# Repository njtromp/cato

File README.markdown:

# What's it all about
This project started slightly after I bought a sail boat, an Amigo 27 to be precisely.
At the time I bought the boat I did notice that the log (speed indicator) was not working
but that didn't bother me much. There where much, more important things, that needed my
attention. It is a mechanical VDO SumLog. There where two reasons for the log not to function.

1. a broken inner cable
2. a rusted impeller that does not turn

These two causes combined with the fact that replacement parts are hard to get your hands on
and the fact that I had a spare GPS Bluetooth dongle started me thinking. What if I can use
the GPS dongle for determining the speed and have a small (like a Raspberry PI) computer
control a electronic motor that drives the speed gauge?

## From RPM to knots and visa versa
I run some experiments using a cordless screwdriver for determining the RPM/knots settings.
It turned out to be about 100 RPM per knot :-). 

# Components
I needed some different components to get everything working

## Hardware
* a small computer
* a Bluetooth GPS dongle
* a USB Bluetooth dongle, for connecting the GPS to the computer
* a motor control unit that is capable of driving the electronic motor
* a electronic motor that is capable of runnning at 800-900 RPM with enough torque that will
be attached to the remainder of the inner cable
* a speed sensor for determining the RPM of the electronic motor (needed for feedback loop)

After some Googling and browsing the internet I come to the following shoppinglist:

* a Raspberry PI B+ (small, low power consumption, 4 USB ports, capable of running Debian)
* a small Bluetooth dongle
* a powerfull electro motor (capble of running at 13000 RPM and a torque of about 0.15 Nm)
* a AdaFruit PWM board based upon a PCA9685 chip
* a power mosfet that will be driven by the AdaFruit board and that will drive the engine
* a good old power transistor 2N3055 and a 12V zener-diode that will ensure that the voltage that
is supplied to the electro motor will stay constant and within the allowed range
* a IR photomicrosensor that can be used for detecting the RPM of the electro motor

I also bought a USB WiFi dongle that will be used for providing a small local WiFi network.  

## Software
* a program that reads the speed information from the GPS dongle and adjusts the speed of
the electronic motor

Although I am a Java Software Engineer by trade I wanted to use a language that has a smaller
memory footprint. After experimenting with Python and NodeJS I chose NodeJS. There are a
lot of modules available for it that integrate with GPSD for example. An other thing that I
like is the fact that the JavaScript is compiled to native code by the V8 engine prior to
running the code.

# Putting it all together
Back in highschool I played a lot around with electronic components and used a soldering iron
for repairing TVs, radios etc. so with I little luck I should still be able to get the
hardware connected. The software proved to be quite easy although being used to a statically
typed language is challenging a loosely typed language needs more trial and error then I am
used to. After some experimenting and using the soldering iron after 25 years I had a prototype
that seemed to be working. During the first trials I discovered that the electro motor was
having a difficult time working at low speeds, typically below 200-300 RPM.

## First improvements (dual power setting)
The problems at low RPMs are caused by the low duty-cycle of the PWM. In order to get the
duty-cycle up the engine must run using a lower voltage. Because I already was using a very
simple voltage stabilizing component (the 2N3055 and the zener-diode) it was relatively easy
to add a extra transistor and a second zener-diode (5V this time) to the existing voltage
stabilizing circuit. This change needed a software counterpart as well. The program must be
able to switch between the voltages at which the engine is running. In order to prevent the
system from switching back and forth between the two different power settings some sort of
delay was needed between the moment the first switch was needed and the actual switching.
The first trials with this new power switching module showed a flaw in the motorcontrol
program. When the power setting was switched from low voltage (5V) to high voltage (12V)
the engine initially was spinning at around 900 RPM (which is equal to 9 knots!) while
prior to the switch is was running at around 300 RPM. Within seconds this was corrected by
the feedback loop but it was not the behavior I wanted. Measuring the duty-cycle at low
voltage and high voltage with the some target RPM showed that there seems to be a 10 to 3
ratio between the duty-cycles. With the control program correcting the duty-cycle when
switching between the power settings lead to a small jitter that is for now within
acceptable ranges.  

## Second improvements (wireless instruments application)
As mentioned before I also bought a USB WiFi dongle. The purpose of this dongle is to have
the Raspberry PI act as a WiFi hotspot that should provide internet connection (through USB
tethering) to everybody on board as long as my phone as a proper internet connection.
Besides provinding internet access this lead to the idea of a small web application that
would use the GPS information for showing the speed and location on any connected device.

# Where to go next
Up till now everything seems to be working. Everything is still in beta phase but for me it
is working fine. Because I was not very familiar with NodeJS and used a whole lot of mixed
quality examples and made some wrong design decisions in the early stages of the project
the whole project needs a major overhaul.

## Code overhaul
* write my own NMEA handling/parsing. I haven't found a NodeJS module that handles NMEA
messages in a way I like (mind you that I am coming from a statically typed language).
* introduce a easier extensible software architecture (NMEA event bus)
* get rid of the tightly coupling between NMEA parsing, motor control, powerswitching and
the instruments application

# TODO
* add some pictures
* add some electronic diagrams
* log the NMEA message on the Raspberry PI for later usage by other applications, OpenCPN
for example

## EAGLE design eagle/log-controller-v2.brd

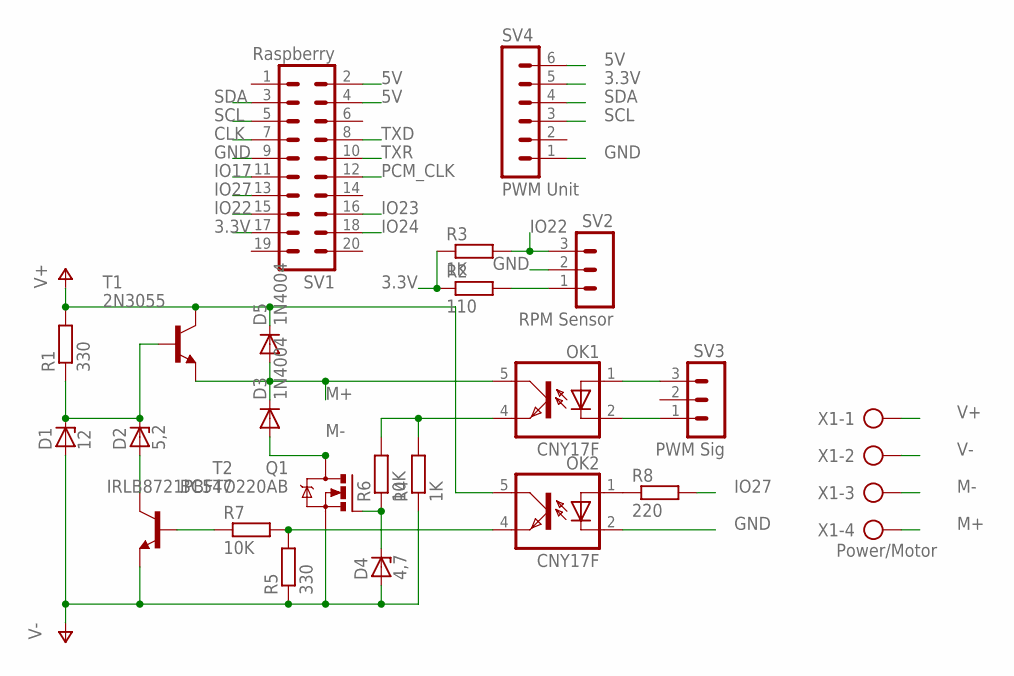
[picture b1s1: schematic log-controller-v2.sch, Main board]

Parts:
D1: 12; DO34Z7
D2: 5,2; DO34Z7
D3, D5: 1N4004; DO41-10
D4: 4,7; DO34Z7
OK1, OK2: CNY17F; DIL06
Q1: IRLB8721PBFTO220AB; TO220AB
R1, R5: 330; 0207/12
R2: 110; 0207/10
R3: 1K; 0207/10
R4: 1K; 0207/12
R6, R7: 10K; 0207/12
R8: 220; 0207/10
SV1: Raspberry; MA10-2
SV2: RPM Sensor; MA03-1
SV3: PWM Sig; MA03-1
SV4: PWM Unit; MA06-1
T1: 2N3055; TO3
T2: BC547; TO92
X1: Power/Motor; AK300/4

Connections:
3.3V: R2.1, R3.1, SV1.17, SV4.5
5V: SV1.2, SV1.4, SV4.6
CLK: SV1.7
GND: OK2.2 (C), SV1.9, SV2.2, SV4.1
IO17: SV1.11
IO22: R3.2, SV1.15, SV2.3
IO23: SV1.16
IO24: SV1.18
IO27: R8.2, SV1.13
M+: D3.C, D5.A, OK1.5 (COL), T1.E, X1.4
M-: D3.A, Q1.D, X1.3
unnamed: D1.C, D2.C, R1.1, T1.B
unnamed: D2.A, T2.3 (C)
unnamed: OK1.4 (EMIT), R4.2, R6.2
unnamed: R2.2, SV2.1
unnamed: OK1.1 (A), SV3.3
unnamed: OK1.2 (C), SV3.1
unnamed: OK2.4 (EMIT), R5.2, R7.2
unnamed: R7.1, T2.2 (B)
unnamed: D4.C, Q1.G, R6.1
unnamed: OK2.1 (A), R8.1
PCM_CLK: SV1.12
SCL: SV1.5, SV4.3
SDA: SV1.3, SV4.4
TXD: SV1.8
TXR: SV1.10
V+: D5.C, OK2.5 (COL), R1.2, T1.C, T1.C/ (C), X1.1
V-: D1.A, D4.A, Q1.S, R4.1, R5.1, T2.1 (E), X1.2

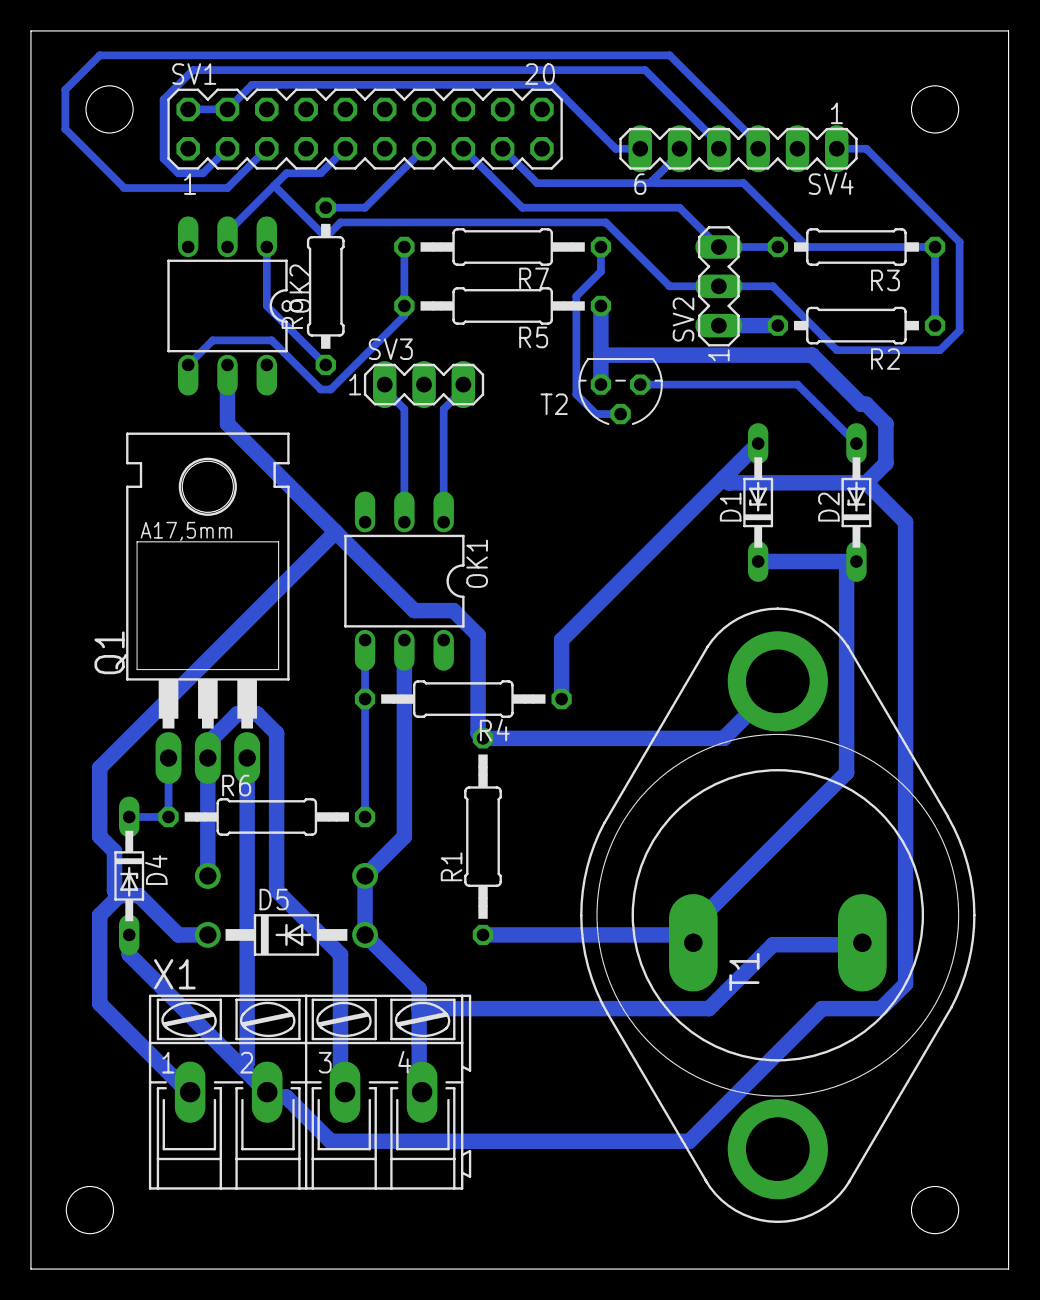
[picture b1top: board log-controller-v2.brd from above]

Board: 2 copper layers, 63.2 x 80.0 mm, 23 parts (1 on the bottom side), 21 nets.

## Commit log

2015-03-12 Initial commit with a working correctDateTime.js.
2015-03-13 Switched to better structure of the code
2015-03-13 Removed old version of 'correctDataTime.js' that was moved to 'correctClock.js'.
2015-03-13 Adopting Node.js naming conventions for files/modules.
2015-03-13 Refactored the code for future separation of concerns.
2015-03-13 Added shutdown button via Node.js :-)
2015-03-13 Added more startup scripts.
2015-03-14 Added jitter detection.
2015-03-18 Implementing own motor control. The PCA9685 module contains errors and has some timing issues that need to be handled.
2015-03-18 Looping through led dim cycle.
2015-03-18 Cleanup of code
2015-03-29 Trying to switch to nano seconds....
2015-03-29 Using millseconds for RPM sensor.
2015-03-29 Displaying milliseconds for every 1/6th rotation.
2015-03-29 Swichted to nanosecond measuring.
2015-03-30 RPM sensor will be used by another module, not by Cato directly
2015-03-30 Corrected type-o
2015-03-30 Added gracefull shutdown module (WIP!)
2015-03-30 Converted unto logging RPM.
2015-04-05 Added datasheets for the electronic parts.
2015-04-05 Refactored the motor and pwm modules.
2015-04-05 Moved line that handles debugging into a more appropriate location.
2015-04-06 Sensor is working.
2015-04-06 Updated JavaScript doc on some functions.
2015-04-07 Refactored code so the global THIS variable is no longer needed.
2015-04-07 Tweaked motor control so it is able to drop the RPM till 100.
2015-04-07 Renamed motor to rpm-controller.
2015-04-07 Refactoring the rpm-controller.
2015-04-07 Extracted creation into separate module
2015-04-07 Cleaning and adding JavaScriptDoc.
2015-04-08 Renamed log-factory to factory.
2015-04-08 Added calibration module.
2015-04-08 Scaffolding for calibration done.
2015-04-08 Calibration should be working.
2015-04-08 Restructed the calibration configuration.
2015-04-08 Moved datasheets to other folder.
2015-04-08 Switched to actual working version.
    The previous ones had some 'require' lines placed as comments.
2015-04-08 Added speed to RPM convertor.
2015-04-08 Made the speeds all Doubles.
2015-04-08 Putting it all together...
2015-04-08 Unified the 'require' usage.
2015-04-09 Made the code more readable and added some tiny testing features.
2015-04-09 Fixed issues that prevented 'calibrate' not to function.
2015-04-09 Starting to behave as expected :-)
2015-04-09 Made more flexible and self explaning.
2015-04-09 Used better naming.
2015-04-09 Removed unneeded options.
2015-04-09 Adjusted to debug settings so we see something about what is going on.
2015-04-10 Documentation added and some minor refactoring.
2015-04-10 Implemented unstable fix handler that will set the speed to 0 if there is no stable speed fix withing 5 seconds.
2015-04-17 Extracted configuration into separate config file.
2015-04-17 Added some comment and prevented a compilation error.
2015-04-21 Added some possible exit traps, need more investigation.
2015-04-25 Added readme
2015-04-25 First 'real' calibration settings.
2015-04-25 Added controlled stopping.
2015-06-05 Added configuration document and updated comments in some files.
2015-06-07 Added more installation instructions.
2015-06-07 Added the folder 'node_modules' .gitignore file.
2015-06-07 Multiple changes / improvements
    - Added a powerswitch that makes it possible to keep de duty cycle relatively high for the same RPM by limiting the voltage for the motor.
    - Added a calculator that can calculate the distance and based on two positions
    - Converted some hardcoded values into configuration items.
2015-06-07 Added the folder '.cache' to .gitignore.
2015-06-08 Changed config so that Sublime workspace file is not tracked anymore.
2015-06-10 Introduced limiting the voltage for the electronic engine when running at low RPM (currently < 300 RPM).
    And moved more settings into the 'config.json' file.
2015-06-11 Corrected device name to match current setup
2015-06-11 Added some more installation instructions.
2015-06-12 Updated installation instructions
2015-06-15 Started hostapd and dnsmasq instructions
2015-06-17 Added some documents about configuring a Raspberry PI to become accesspoint
2015-06-17 Started development for a Node server that will provide a responsive HTML page for speed, direction etc.
2015-06-18 Started taking care of the TODOs
2015-06-18 Small test app.
2015-06-21 Added more documentation.
2015-06-21 Started using Bootstrap.
2015-06-21 Adding a second gauge (for the average speed).
2015-06-23 Made de handling for HTML files a little smarter and introduced a second speed gauge.
2015-06-24 Moved scripts to the bottom and made the client callback server agnostic.
2015-06-25 Started creating a raw NMEA listener that can be used to calculate the average speed
2015-07-19 Removed temporary testing file.
2015-07-19 Some more tests for stabilising the WiFi connection.
2015-07-19 Corrected a log statement.
2015-07-19 Enabled the log-controller by default.
2015-07-19 Adjusted according to actual settings.
2015-07-19 Silencing the log-controller.
2015-07-21 Calibration info for current setup.
2015-07-21 Improved English (hopefully ;-) ).
2015-07-30 Attempting to cope more gentle with voltage switching. Currently the motor spins either out of control or comes to a dead stop when switching.
2015-07-30 Added config for improved voltage switching.
2015-07-30 Latest config from Cato.
2015-07-30 Debugged and improved the voltage switching behaviour!
2015-08-09 Integrated the server with the existing code.
    Very rough. Needs a complete overhaul.
2015-08-10 Removed unneeded loggin info.
2015-08-10 Now the position is formatted.
2015-08-10 Added padding the the degrees and whole minutes.
2015-08-10 Added some info on installing and configuring Apache2 as a reverse proxy.
2015-08-10 Update to-do list :-(
2015-08-10 Corrected a small bug in the to-do list.
2015-08-13 Some small improvements
2015-08-15 Started documenting the project.
2015-08-15 Trying to get the layout working.
2015-08-15 More small adjustments.
2015-08-15 Even more little improvements.
2015-08-15 Added a missing hardware component ;-)
2015-08-16 Added more info.
2015-08-16 Added more information.
2015-08-16 Some improvements.
2015-08-16 Moved some unused files to the attic and added a lot of extra information to the readme file.
2015-08-17 Corrections.
2016-01-22 Cleaning up.
2016-02-09 More datasheets added and removed a feature (the reset/shutdown button) that is not needed any more.
2016-02-13 Text corrections.
2016-02-17 Corrected a problem when the battery is running low and a transition is made to run in lose-power mode.
2016-02-17 Preparation for the new PCB. On this new PSB the power switch is connected to GPIO27.
2016-02-25 Sample for 3D printing a case.
    Just contains the mounting points for the log controller.
2016-02-25 Some type-o corrections.
2016-02-25 A small improvement (less code).
2016-02-25 Playing with OpenSCAD to create a better RPM sensor disk.
2016-02-25 Looking good.
2016-02-25 Final prototype. Already printed :-)
2016-02-25 Result of a small error, should have been renamed to 'rpm-sensor-disk'.
2016-02-26 Made more flexible.
2016-02-26 Renamed some parameters and move some comments around.
2016-02-26 Converted into module.
2016-02-26 Added PCB and electronic schema.
2016-02-26 Started with motor mount design.
2016-06-26 Corrected case-error, looks like Math.Min does not exist. Math.min should be the correct.
2016-06-27 Added a lot of installation inforamtion.
2016-06-27 Added pin layout picture
2016-06-27 Rearranged instructions.
2016-06-27 Preparing for the Adafruit Ultimate GPS module.
2016-06-29 Updated installation instructions with Adafruit GPS module and NTPD/GPSD.
2016-06-29 Added documentation for the Adafruit GPS module.
2016-06-30 Looks like everything startup at boot.
2016-06-30 Finalizing the setup.
2016-06-30 More null-safe.
2016-06-30 Corrected formatting error.
2016-07-01 Some more padding issues fixed.
2016-07-01 Moved some some test apps to a more appropriate location.
2016-07-03 Started with the big overhaul....
2016-07-03 Added some Apache confgiruation to ensure a better experience.
2016-07-03 Node v0.12 seems to be unable to handle 'const' keyword :-(
2016-07-03 Trying different exports clause in the hop the Raspbian Node version is supporting it...
2016-07-03 Down graded to node v0.12.6.
    The Raspberry PI is running this version so it must be compatible with
    v0.12.6!
2016-07-05 Added unit tests and implemented more RMC message methods.
2016-07-05 Corrected lat/long calculations.
2016-07-05 Introduced date/time methods.
2016-07-06 Reversed embedded variable usage in error message, it didn't work.
2016-07-07 Restructuring of the folders and some minor corrections in text.
2016-07-10 Added more messages (ZDA) and tests.
2016-07-10 Added GGA message and tests.
2016-07-10 Corrected some internal numbering and added some tests.
2016-07-10 Tests for Checksum added.
2016-07-10 Added tests for DateHelper.
2016-10-27 Al lot of changes from a couple of month ago, don't know exactly what and why.
2016-10-27 Some small fixes, mainly layout.
2016-10-27 Changed a resistor due to the electronic gearbox not working.
    Seems not to have solved it completely... back to the drawing board.
